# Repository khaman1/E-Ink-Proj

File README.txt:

PCB.pcbdoc: the pcb file designed by Altium Designer
Gerber.cam: file Gerber exported from PCB.pcbdoc
NC Drills: Drilling map exported from PCB.pcbdoc

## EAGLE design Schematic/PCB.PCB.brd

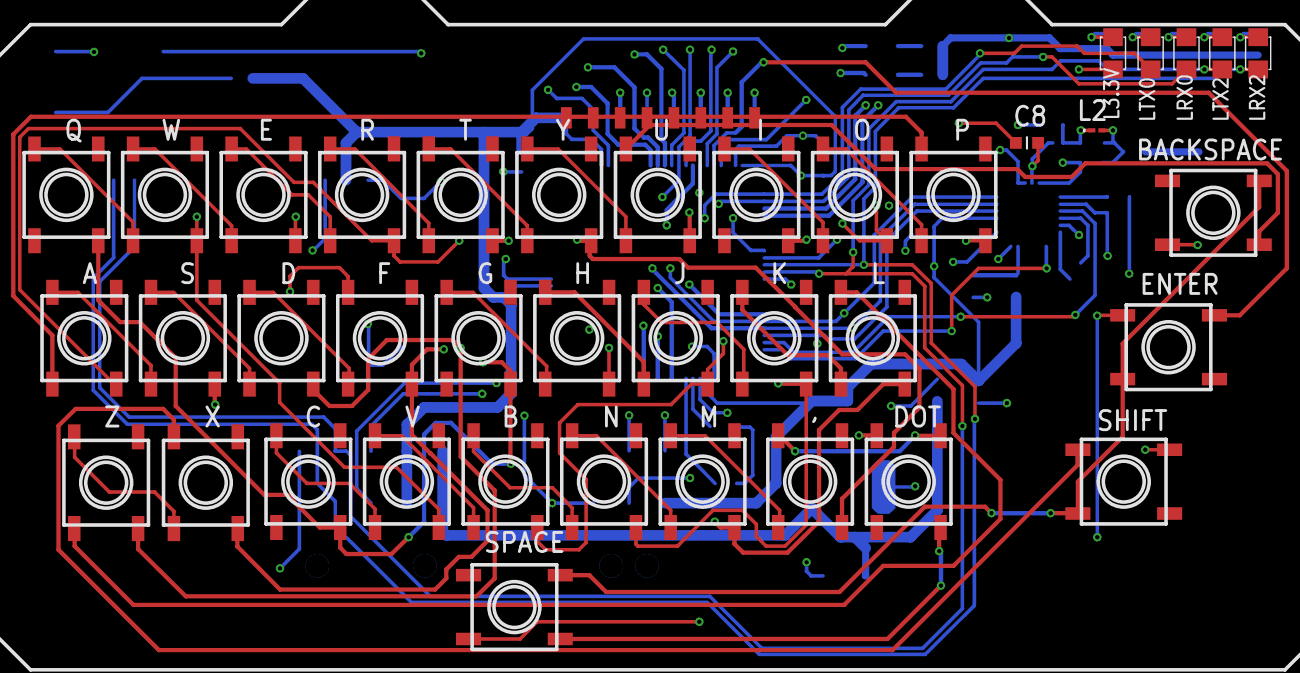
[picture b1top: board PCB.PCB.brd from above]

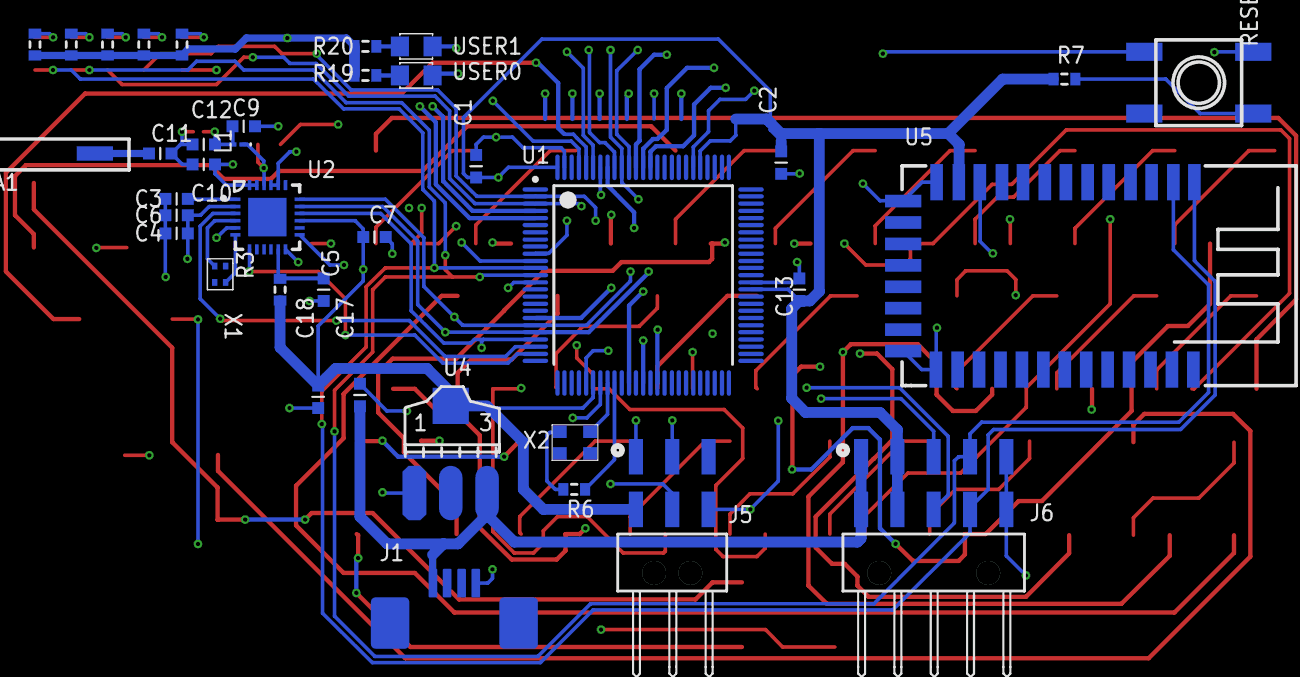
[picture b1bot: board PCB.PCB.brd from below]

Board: 2 copper layers, 78 parts (38 on the bottom side), 10 nets.

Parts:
,: SW; KHA_BUTTON_1PRIMARY
A: SW; KHA_BUTTON_1PRIMARY
A1: Antenna; ANTENNA_1PRIMARY
B: SW; KHA_BUTTON_1PRIMARY
BACKSPACE: SW; KHA_BUTTON_1PRIMARY
C: SW; KHA_BUTTON_1PRIMARY
C1, C2, C3, C4, C5, C6, C7, C8, C9, C10, C11, C12, C13, C17, C18: approved_sub_OK; SMD-0603C_1PRIMARY
D: SW; KHA_BUTTON_1PRIMARY
DOT: SW; KHA_BUTTON_1PRIMARY
E: SW; KHA_BUTTON_1PRIMARY
ENTER: SW; KHA_BUTTON_1PRIMARY
F: SW; KHA_BUTTON_1PRIMARY
G: SW; KHA_BUTTON_1PRIMARY
H: SW; KHA_BUTTON_1PRIMARY
H2: EInk_LCD_Module; EINK_MODULE_1PRIMARY
I: SW; KHA_BUTTON_1PRIMARY
J: SW; KHA_BUTTON_1PRIMARY
J1: USB_Micro_Type_B; ZIF_CONN_4P_TE84953-4_1PRIMARY
J5: 06p; 610106249121_1PRIMARY
J6: 10p; 610110249121_1PRIMARY
K: SW; KHA_BUTTON_1PRIMARY
L: SW; KHA_BUTTON_1PRIMARY
L1, L2: Inductor; 0603_1PRIMARY
L3.3V: LED_SMD; SM-LED-0805-BLUE_1PRIMARY
LRX0, LRX2: LED_SMD; SM-LED-0805-BLUE_1PRIMARY
LTX0, LTX2: LED_SMD; SM-LED-0805-BLUE_1PRIMARY
M: SW; KHA_BUTTON_1PRIMARY
N: SW; KHA_BUTTON_1PRIMARY
O: SW; KHA_BUTTON_1PRIMARY
P: SW; KHA_BUTTON_1PRIMARY
Q: SW; KHA_BUTTON_1PRIMARY
R: SW; KHA_BUTTON_1PRIMARY
R3, R4, R6, R7, R17, R18, R19, R20, R21, R22: Res3; J1-0603_1PRIMARY
RESET: SW; KHA_BUTTON_2PRIMARY
S: SW; KHA_BUTTON_1PRIMARY
SHIFT: SW; KHA_BUTTON_1PRIMARY
SPACE: SW; KHA_BUTTON_1PRIMARY
T: SW; KHA_BUTTON_1PRIMARY
U: SW; KHA_BUTTON_1PRIMARY
U1: ATmega2560-8AU-3.3V; 100A_N_1PRIMARY
U2: SX1280; SX1280_QFN24_4X4_1PRIMARY
U4: AMS1117_3.3V; AMS1117_1PRIMARY
U5: Bluetooth_HM-12; HM-12_1PRIMARY
USER0, USER1: LED_SMD; SM-LED-0805-BLUE_1PRIMARY
V: SW; KHA_BUTTON_1PRIMARY
W: SW; KHA_BUTTON_1PRIMARY
X: SW; KHA_BUTTON_1PRIMARY
X1: 52Mhz; CRYSTAL_52MHZ_1PRIMARY
X2: 8MHz; PCBCOMPONENT_1_1PRIMARY
Y: SW; KHA_BUTTON_1PRIMARY
Z: SW; KHA_BUTTON_1PRIMARY

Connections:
3.3V: J6.2, J6.7, U5.12
5V: J1.2, J6.1, J6.6, U4.3
GND: J6.5, J6.10, U5.21, U5.22
HM-12-RESET: U1.14, U5.11
MISO: J5.1, U1.22
RXD0: J6.8, U1.2
RXD2: J6.9, U1.12, U5.1
TXD0: J6.3, U1.3
TXD2: J6.4, U1.13, U5.2
XTAL1: R6.2, U1.34

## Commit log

2017-09-19 :confetti_ball: Added .gitattributes & .gitignore files
2017-09-19 Init
2017-10-04 Update 10/04/2017
2017-10-07 Update RTOS
2017-10-23 Update ESP32 and new schematic
